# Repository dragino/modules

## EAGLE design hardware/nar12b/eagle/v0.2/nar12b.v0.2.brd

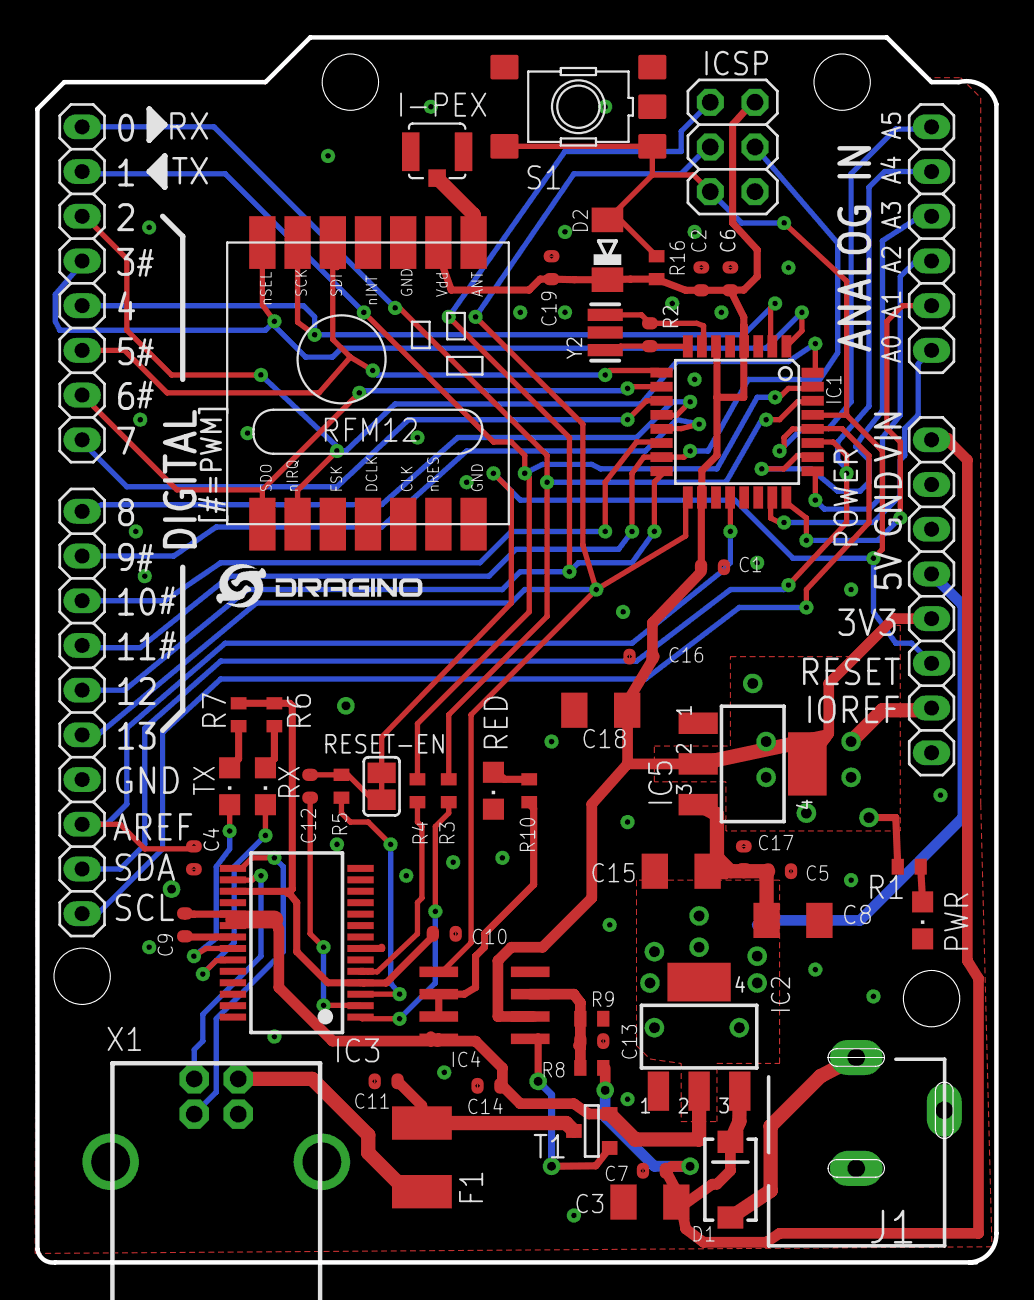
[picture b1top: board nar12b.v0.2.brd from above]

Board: 2 copper layers, 54.5 x 69.6 mm, 56 parts (0 on the bottom side), 48 nets.

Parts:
AD: 6x1F-H8.5; 1X06
C1, C2, C4, C5, C6, C9, C10, C11, C12, C13, C14, C16, C19: 100n; C0402
C3, C8, C15, C18: 10uF; C1206K
C7, C17: 100n-NL; C0402
D1: SS14; SMA-DIODE
D2: CD1206-S01575; MINIMELF
F1: 500ma; L1812
I-PEX: I-PEX
IC1: ATMEGA168-20AU; SMARTPRJ_TQFP32-08
IC2: BL1117-50CX; SOT223
IC3: FT232RL; SSOP28
IC4: LMV358D; SO08
IC5: BL1117-33CX; SOT223
ICSP: 3x2 M; 2X03
IOH: 10x1F-H8.5; 1X10@1
IOL: 8x1F-H8.5; 1X08
J1: 12V_VIN; POWER_JACK_SLOT
POWER: 8x1F-H8.5; 1X08
PWR: CHIPLED_0805
R1, R8, R9, R16: 10K; R0402
R2: 1M; R0402
R3, R4, R6, R7, R10: 1K; R0402
R5: 100_NL; R0402
RED: CHIPLED_0805
RESET-EN: SJ
RX: CHIPLED_0805
S1: TS42
T1: FDN340P; SOT-23
TX: CHIPLED_0805
U$1: LOGO-NEW; LOGO-SILK-NEW
U$2: RFM12_SMDSMD; RFM12
X1: PN61729
Y2: CSTCE16M0V53-R0 16MHZ; RESONATOR

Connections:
3.3V: C1.1, C2.1, C6.1, C16.1, C18.1, C19.2, D2.C, IC1.4, IC1.6, IC1.18, IC4.2, IC5.2, IC5.4, ICSP.2, POWER.2, POWER.4, R1.2, R16.2, U$2.9
3.3V1: C10.2, IC3.4, IC3.17, R6.1, R7.1
5V: C5.1, C8.1, C9.1, C14.1, C15.1, C17.1, IC2.2, IC2.4, IC3.19, IC3.20, IC4.8, IC5.3, POWER.5, T1.2
/RST: C12.1, D2.A, IC1.29, ICSP.5, POWER.3, R5.1, R16.1, RESET-EN.1, RESET-EN.2, S1.1, S1.2
/SEL: IC1.1, IOL.4, U$2.14
AD0: AD.1, IC1.23
AD1: AD.2, IC1.24
AD2: AD.3, IC1.25
AD3: AD.4, IC1.26
AD4/SDA: AD.5, IC1.27, IOH.9
AD5/SCL: AD.6, IC1.28, IOH.10
AREF: C4.2, IC1.20, IOH.8
AVR_RXD: IC3.1, R3.2
AVR_TXD: IC3.5, R4.2
CMP: C13.1, IC4.3, R8.1, R9.2
GND: C1.2, C2.2, C3.2, C4.1, C5.2, C6.2, C7.2, C8.2, C9.2, C10.1, C11.2, C13.2, C14.2, C15.2, C16.2, C17.2, C18.2, C19.1, I-PEX.GND, I-PEX.GND1, IC1.3, IC1.5, IC1.21, IC2.1, IC3.7, IC3.18, IC3.21, IC3.25, IC3.26, IC4.4, IC5.1, ICSP.6, IOH.7, J1.GND@1, J1.GND@2, POWER.6, POWER.7, PWR.C, R9.1, RED.C, S1.3, S1.4, U$2.7, U$2.10, X1.4, X1.P$1, X1.P$2, Y2.2
MISO: IC1.16, ICSP.1, IOH.5
MOSI: IC1.15, ICSP.4, IOH.4
unnamed: D1.A, J1.PWR
unnamed: PWR.A, R1.1
unnamed: IC3.16, X1.2
unnamed: IC3.15, X1.3
unnamed: F1.2, X1.1
unnamed: IC3.3, R5.2
unnamed: IC3.23, RX.C
unnamed: C12.2, IC3.2
unnamed: IC3.22, TX.C
unnamed: R6.2, RX.A
unnamed: R7.2, TX.A
unnamed: IC4.1, T1.3
unnamed: IC4.6, IC4.7, R10.2
unnamed: R10.1, RED.A
unnamed: I-PEX.SIG, U$2.8
PB0: IC1.12, IOH.1
PB1: IC1.13, IOH.2
PD0: IC1.30, IOL.1, R3.1
PD1: IC1.31, IOL.2, R4.1
PD7: IC1.11, IOL.8
RF_/IRQ: IC1.32, IOL.3, U$2.2
RF_SCK: IC1.2, IOL.5, U$2.13
RF_SDI: IC1.9, IOL.6, U$2.12
RF_SDO: IC1.10, IOL.7, U$2.1
SCK: IC1.17, IC4.5, ICSP.3, IOH.6
SS: IC1.14, IOH.3
USBVCC: C11.1, F1.1, T1.1
VIN: C3.1, C7.1, D1.C, IC2.3, POWER.8, R8.2
XTAL1: IC1.7, R2.1, Y2.3
XTAL2: IC1.8, R2.2, Y2.1
